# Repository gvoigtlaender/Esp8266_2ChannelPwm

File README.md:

# Esp8266_2ChannelPwm
## ESP8266 based 2-Channel LED Controller 
* ESP12F 
* LM2596S step-down converter
* 2 PWM Channels (white & blue light)
* AO3400A N-Channel MOSFET to directly drive LEDs (tested with 24V 1A)
* onboard RST button
* connector for PGM button, to be used as general purpose button as well
* connector for THT LED
* JST programming connector
* power in / out soldering with up to 1.75mm diameter
* designed to fit into Hammond Electronics 1551HFLBK 60 x 35 x 20 ABS Euro-Case

## Schematic

## PCB

## Case

## Complete

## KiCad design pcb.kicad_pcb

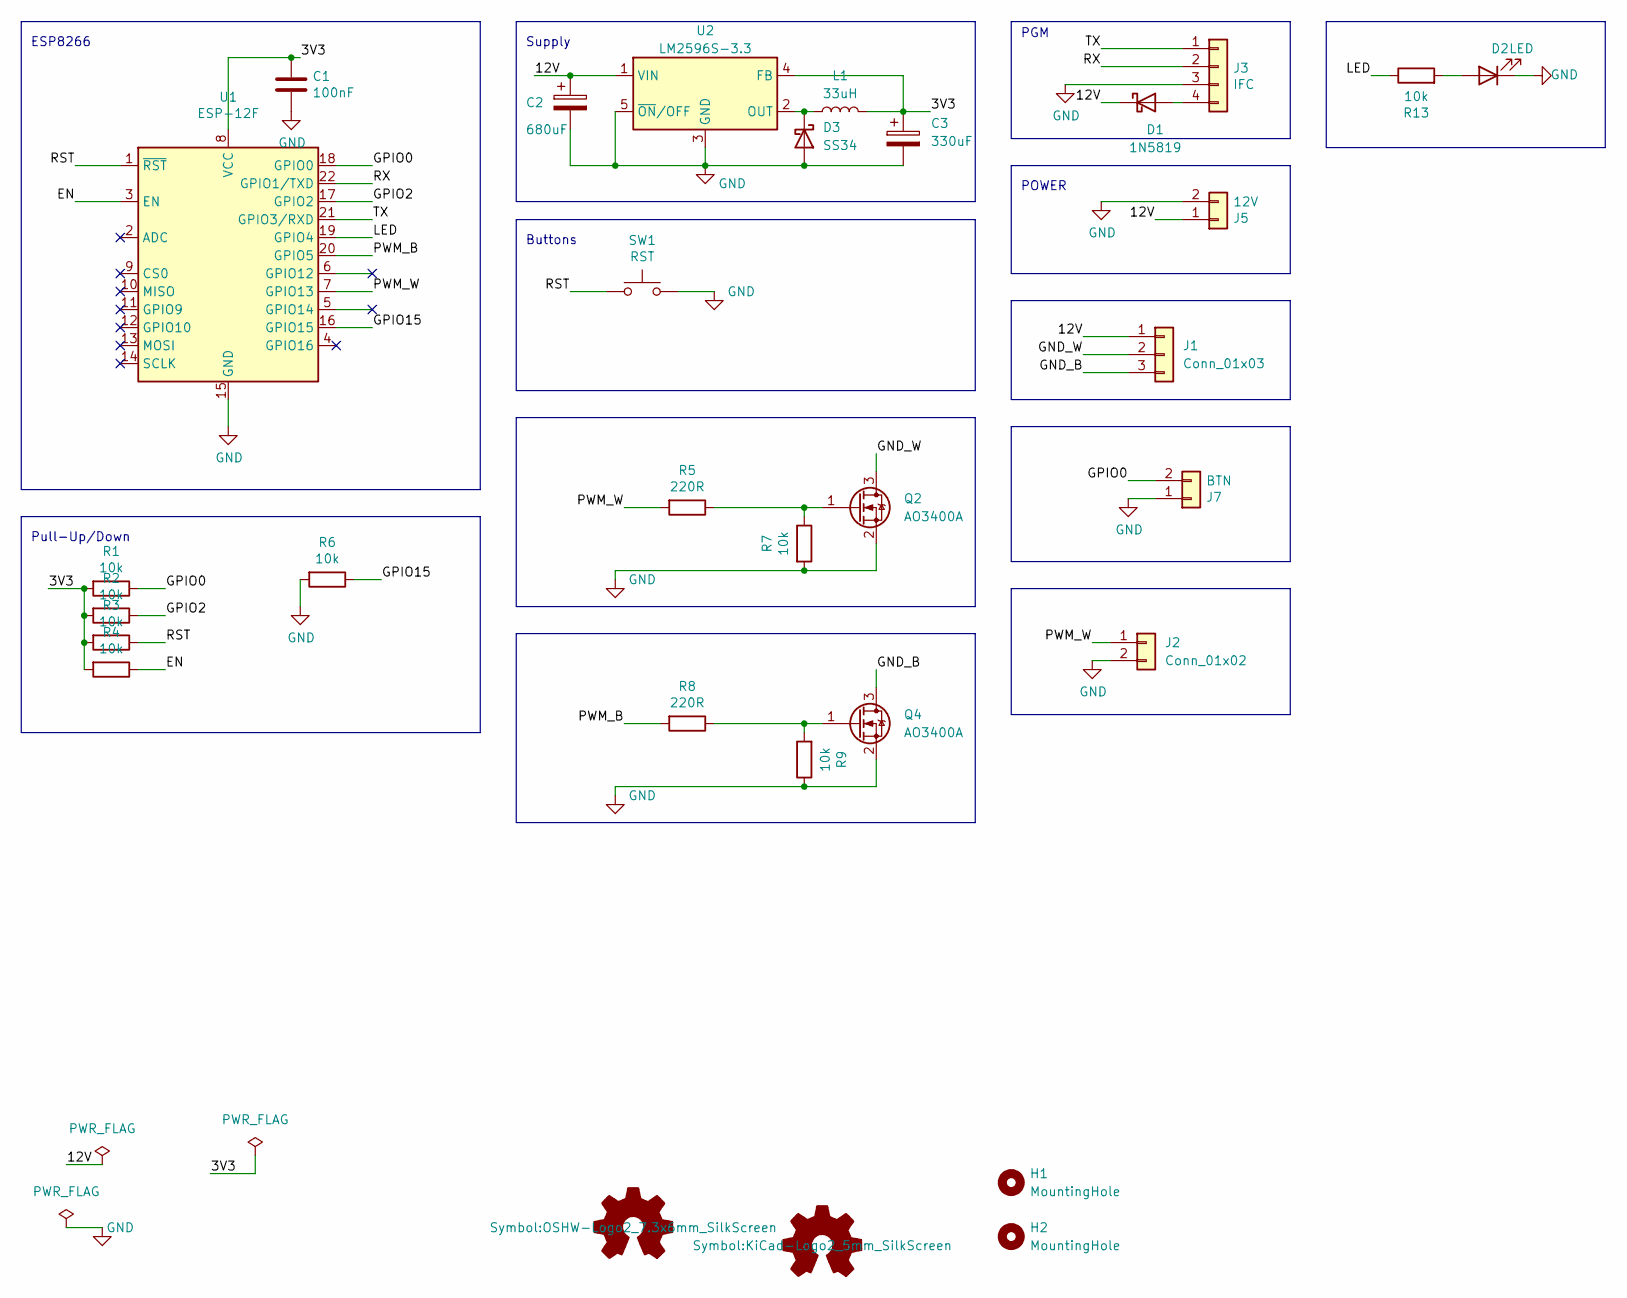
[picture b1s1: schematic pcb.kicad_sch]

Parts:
C1: 100nF; C_0805_2012Metric; LCSC C49678
C2: 680uF; CP_Radial_D4.0mm_P2.00mm
C3: 330uF; CP_EIA-7343-20_Kemet-V
D1: 1N5819; D_SMA
D2: LED; LED_D3.0mm
D3: SS34; D_SMA
H1, H2: MountingHole; MountingHole_2.5mm
J1: Conn_01x03; PinHeader_1x03_P2.54mm_Vertical
J2: Conn_01x02; PinHeader_1x02_P2.54mm_Vertical
J3: IFC; JSTPH4
J5: 12V; PinHeader_1x02_P2.54mm_Vertical
J7: BTN; PinHeader_1x02_P2.54mm_Vertical
L1: 33uH; L_12x12mm_H6mm
Q2, Q4: AO3400A; SOT-23
R1, R2, R3, R4, R6, R7, R9, R13: 10k; R_0805_2012Metric; LCSC C17414
R5, R8: 220R; R_0805_2012Metric; LCSC C17414
SW1: RST; SW_SPST_CK_RS282G05A3
U1: ESP-12F; ESP-12E
U2: LM2596S-3.3; TO-263-5_TabPin3

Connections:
/3V3: C1.1, C3.1, L1.2, R1.2, R2.2, R3.2, R4.2, U1.8 (VCC), U2.4 (FB)
/12V: C2.1, D1.1 (K), J1.1, J5.1, U2.1 (VIN)
/EN: R4.1, U1.3 (EN)
/GND_B: J1.3, Q4.3 (D)
/GND_W: J1.2, Q2.3 (D)
/GPIO0: J7.2, R1.1, U1.18 (GPIO0)
/GPIO2: R2.1, U1.17 (GPIO2)
/GPIO15: R6.1, U1.16 (GPIO15)
/LED: R13.1, U1.19 (GPIO4)
/PWM_B: R8.2, U1.20 (GPIO5)
/PWM_W: J2.1, R5.2, U1.7 (GPIO13)
/RST: R3.1, SW1.1, U1.1 (~RST)
/RX: J3.2, U1.22 (GPIO1/TXD)
/TX: J3.1, U1.21 (GPIO3/RXD)
GND: C1.2, C2.2, C3.2, D2.1 (K), D3.2 (A), J2.2, J3.3, J5.2, J7.1, Q2.2 (S), Q4.2 (S), R6.2, R7.2, R9.1, SW1.2, U1.15 (GND), U2.3 (GND), U2.5 (~ON/OFF)
unnamed: D1.2 (A), J3.4
unnamed: D2.2 (A), R13.2
unnamed: D3.1 (K), L1.1, U2.2 (OUT)
unnamed: Q2.1 (G), R5.1, R7.1
unnamed: Q4.1 (G), R8.1, R9.2

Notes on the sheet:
ESP8266
Buttons
Supply
POWER
PGM
Pull-Up/Down

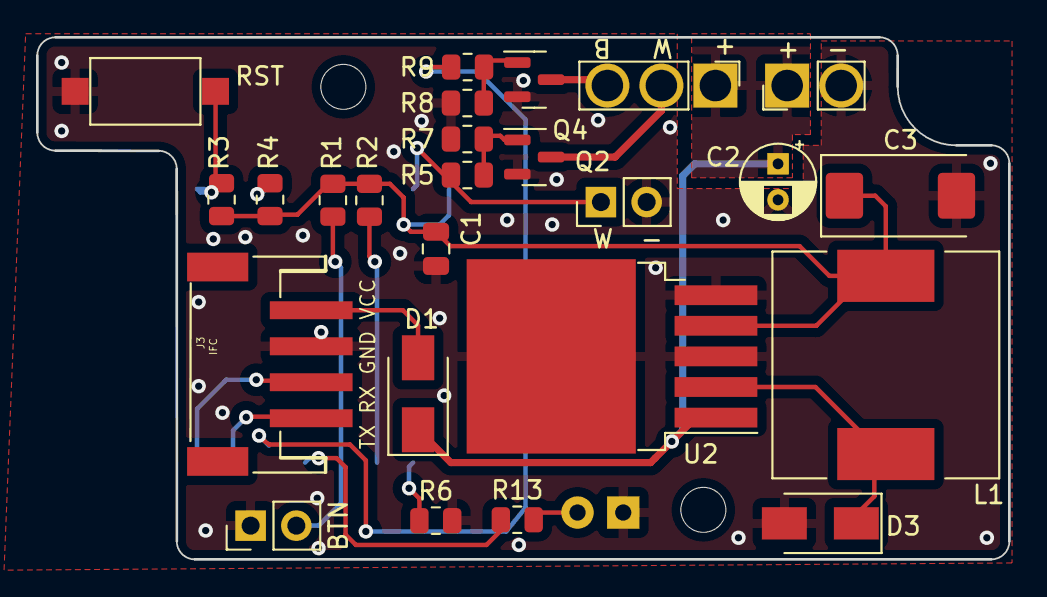
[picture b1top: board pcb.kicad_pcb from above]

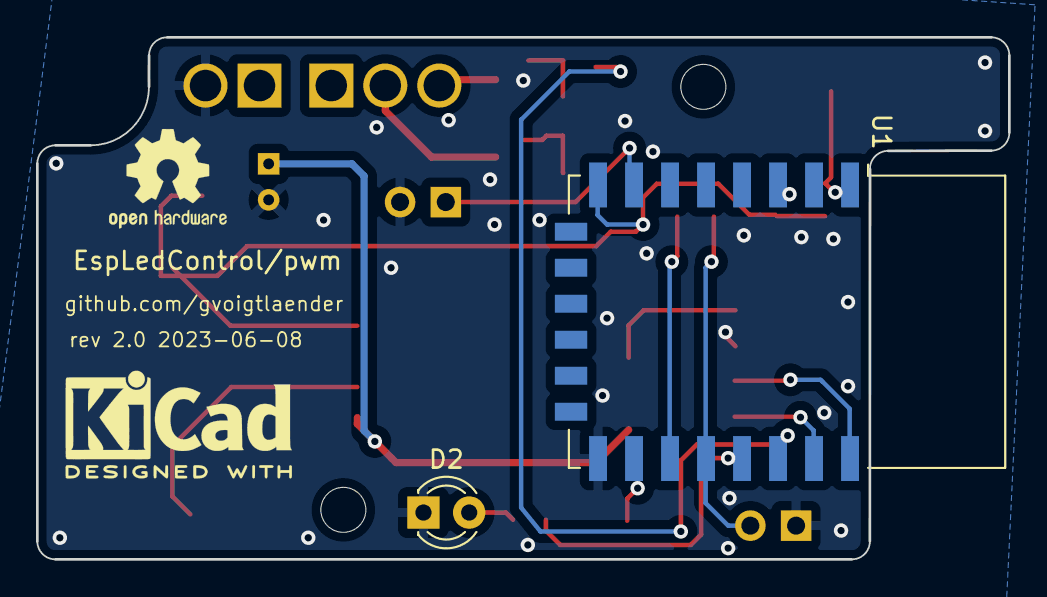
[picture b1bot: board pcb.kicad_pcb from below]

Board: 2 copper layers, 54.0 x 29.0 mm, 29 parts (2 on the bottom side), 20 nets.

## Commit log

2023-07-13 current version
